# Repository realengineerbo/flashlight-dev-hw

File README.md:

# Flashlight Dev Board Hardware

## Introduction

This repository contains design files for the development board for a flashlight boost driver. The test firmware can be found in the [firmware repository](https://github.com/engineerbo/flashlight-dev-fw).

Also included in the `scripts` subdirectory are Python scripts used to calculate component values during the design process, as well as generate the look-up table for brightness settings.

For a detailed explanation of this project, check out the [video series](https://www.youtube.com/playlist?list=PLYK5tmZIBWtEJjwAFE-49hSeELu9zoAmV) on the [Engineer Bo YouTube channel](https://youtube.com/@engineerbo).

## Features

The development board is designed in [KiCad](https://www.kicad.org/), and features the following:

* ATtiny1616 microcontroller
* MP3432 boost converter
* LED current regulation
  * 1R and 10mR current sense resistances, selectable for high dynamic range (HDR)
  * ATtiny1616 DAC controlled current setpoint
  * Current regulation using TLV333/OPA333 op-amp and MP3432 feedback pin
* Power switch multi-click counting
* Temperature sensing
  * NTC thermistor
  * ATtiny1616 internal temperature sensor
* Battery voltage sensing with low current leakage
* Optional potentiometer for current setpoint (highly experimental)
* Test probe hooks
* Headers for all ATtiny1616 pins
* Many jumpers for testing different configurations

## Usage

This development board is meant to serve as a reference for anybody interested in learning about flashlight boost drivers. It's possible to build these boards, but assembly requires reasonable skill and involves less-than-friendly components e.g. DFN, QFN and many 0402 passives.

Instead, I recommend having a look at the schematics, and leave me a comment on [YouTube](https://www.youtube.com/playlist?list=PLYK5tmZIBWtEJjwAFE-49hSeELu9zoAmV) if you have any questions.

## Hardware Revisions

### Revision A

This is the original design built for testing, and includes a couple of issues:

* GPIO driven P-channel MOSFET for HDR MOSFET gate drive
* MP3432 UVLO not configured
* Wrong footprint for NTC thermistor

These issues and their fixes are explained in detail in the [video series](https://www.youtube.com/playlist?list=PLYK5tmZIBWtEJjwAFE-49hSeELu9zoAmV).

### Revision B

Revision B fixes the issues in Revision A:

* GPIO driven N-channel MOSFET for HDR MOSFET gate drive
* Added MP3432 UVLO

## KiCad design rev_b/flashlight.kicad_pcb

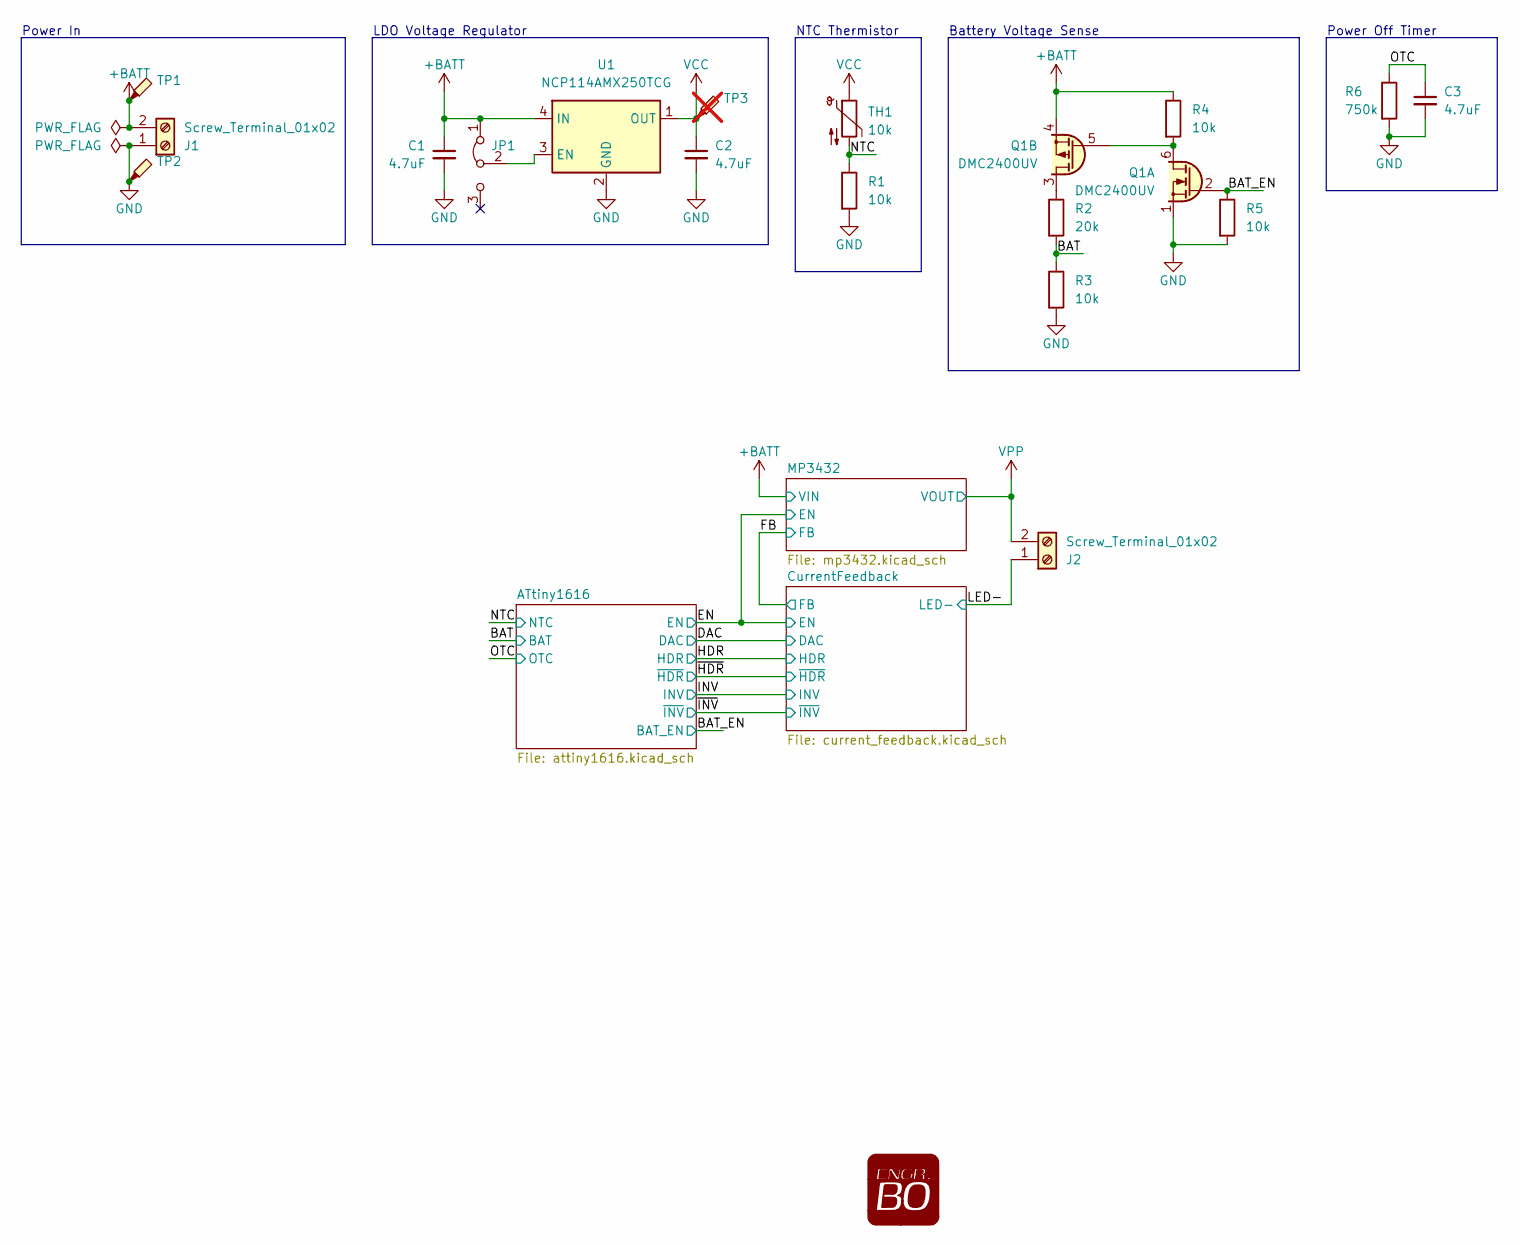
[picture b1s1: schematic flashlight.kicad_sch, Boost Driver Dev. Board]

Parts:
C1, C2, C3: 4.7uF; C_0603_1608Metric; Tolerance X5R; Voltage 16V
J1, J2: Screw_Terminal_01x02; TerminalBlock_Phoenix_MKDS-1,5-2_1x02_P5.00mm_Horizontal
JP1: Jumper_3_Bridged12; PinHeader_1x03_P2.54mm_Vertical
LOGO1: LOGO; logo_6mm
Q1: DMC2400UV; SOT-563
R1, R3, R4, R5: 10k; R_0402_1005Metric; Tolerance 1%
R2: 20k; R_0402_1005Metric; Tolerance 1%
R6: 750k; R_0402_1005Metric; Tolerance 1%
TH1: 10k; R_0402_1005Metric; PartNumber NCP15XH103F03RC
TP1, TP2: TestPoint_Probe; TestPoint_Keystone_5000-5004_Miniature; PartNumber RH-5000
TP3: TestPoint_Probe; TestPoint_Keystone_5000-5004_Miniature; PartNumber RH-5000; not fitted
U1: NCP114AMX250TCG; OnSemi_XDFN4-1EP_1.0x1.0mm_EP0.52x0.52mm; PartNumber NCP114AMX250TCG

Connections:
+BATT: C1.1, J1.2, JP1.1 (A), Q1.4 (S2), R4.1, TP1.1, U1.4 (IN); also elsewhere on the board
/BAT: R2.2, R3.1; also elsewhere on the board
/BAT_EN: Q1.2 (G1), R5.1; also elsewhere on the board
/LED-: J2.1; also elsewhere on the board
/NTC: R1.1, TH1.2; also elsewhere on the board
/OTC: C3.1, R6.1; also elsewhere on the board
GND: C1.2, C2.2, C3.2, J1.1, Q1.1 (S1), R1.2, R3.2, R5.2, R6.2, TP2.1, U1.2 (GND), U1.5 (GND); also elsewhere on the board
unnamed: JP1.2 (C), U1.3 (EN)
unnamed: Q1.5 (G2), Q1.6 (D1), R4.2
unnamed: Q1.3 (D2), R2.1
VCC: C2.1, TH1.1, TP3.1, U1.1 (OUT); also elsewhere on the board
VPP: J2.2; also elsewhere on the board

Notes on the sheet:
NTC Thermistor
Battery Voltage Sense
LDO Voltage Regulator
Power In
Power Off Timer

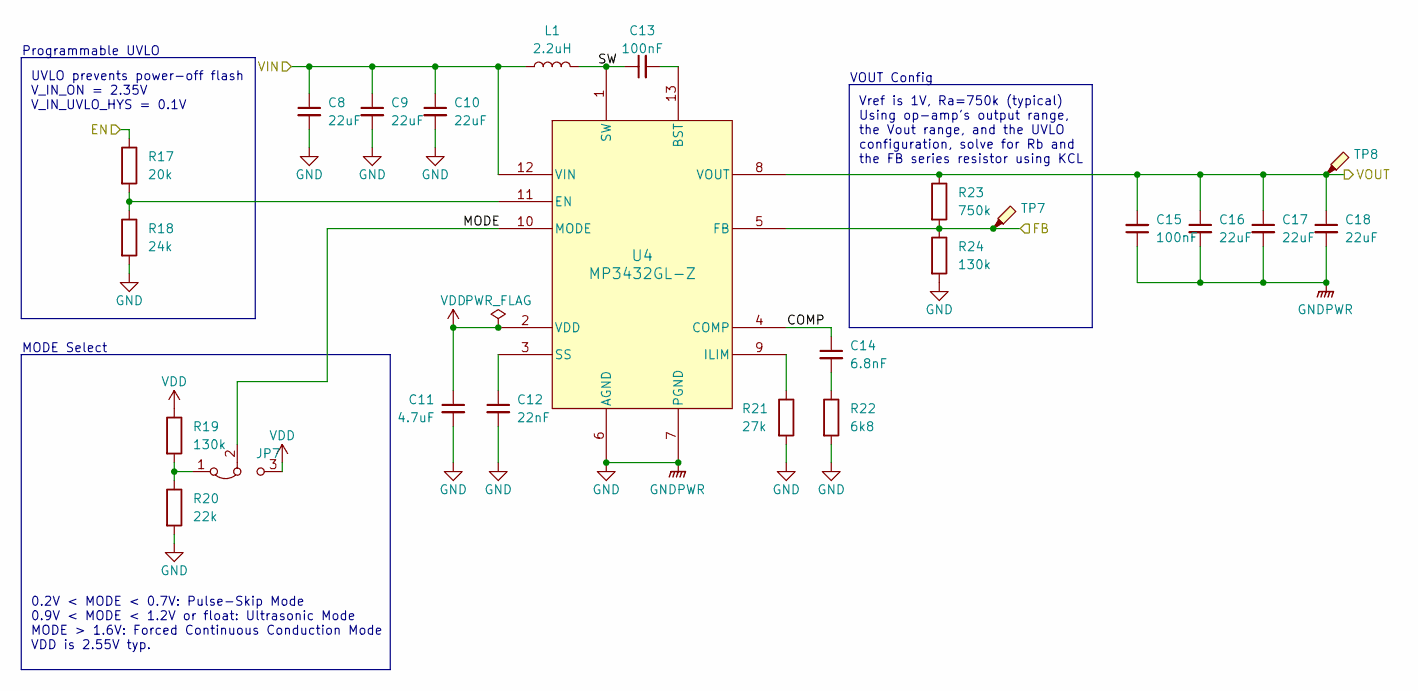
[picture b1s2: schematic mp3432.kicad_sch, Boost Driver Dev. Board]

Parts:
C8, C9, C10, C16, C17, C18: 22uF; C_0805_2012Metric; Tolerance X5R; Voltage 25V
C11: 4.7uF; C_0603_1608Metric; Tolerance X5R; Voltage 16V
C12: 22nF; C_0402_1005Metric
C13, C15: 100nF; C_0402_1005Metric
C14: 6.8nF; C_0402_1005Metric
JP7: Jumper_3_Bridged12; PinHeader_1x03_P2.54mm_Vertical
L1: 2.2uH; L_Coilcraft_XAL7070-XXX; PartNumber XAL7070-222MEC
R17: 20k; R_0402_1005Metric; Tolerance 1%
R18: 24k; R_0402_1005Metric; Tolerance 1%
R19, R24: 130k; R_0402_1005Metric; Tolerance 1%
R20: 22k; R_0402_1005Metric; Tolerance 1%
R21: 27k; R_0402_1005Metric; Tolerance 1%
R22: 6k8; R_0402_1005Metric; Tolerance 1%
R23: 750k; R_0402_1005Metric; Tolerance 1%
TP7, TP8: TestPoint_Probe; TestPoint_Keystone_5000-5004_Miniature; PartNumber RH-5000
U4: MP3432GL-Z; QFN-13_MP3431_MNP; PartNumber MP3432GL-Z

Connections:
+BATT: C8.1, C9.1, C10.1, L1.1, U4.12 (VIN); also elsewhere on the board
/EN: R17.1; also elsewhere on the board
/FB: R23.2, R24.1, TP7.1, U4.5 (FB); also elsewhere on the board
/MP3432/COMP: C14.1, U4.4 (COMP)
/MP3432/MODE: JP7.2 (C), U4.10 (MODE)
/MP3432/SW: C13.1, L1.2, U4.1 (SW)
GND: C8.2, C9.2, C10.2, C11.2, C12.2, C15.1, C16.2, C17.2, C18.2, R18.2, R20.2, R21.2, R22.2, R24.2, U4.6 (AGND), U4.7 (PGND); also elsewhere on the board
unnamed: C14.2, R22.1
unnamed: JP7.1 (A), R19.2, R20.1
unnamed: C13.2, U4.13 (BST)
unnamed: R17.2, R18.1, U4.11 (EN)
unnamed: R21.1, U4.9 (ILIM)
unnamed: C12.1, U4.3 (SS)
VDD: C11.1, JP7.3 (B), R19.1, U4.2 (VDD)
VPP: C15.2, C16.1, C17.1, C18.1, R23.1, TP8.1, U4.8 (VOUT); also elsewhere on the board

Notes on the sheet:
Vref is 1V, Ra=750k (typical) Using op-amp's output range, the Vout range, and the UVLO configuration, solve for Rb and the FB series resistor using KCL
0.2V < MODE < 0.7V: Pulse-Skip Mode 0.9V < MODE < 1.2V or float: Ultrasonic Mode MODE > 1.6V: Forced Continuous Conduction Mode VDD is 2.55V typ.
MODE Select
UVLO prevents power-off flash V_IN_ON = 2.35V V_IN_UVLO_HYS = 0.1V
Programmable UVLO
VOUT Config

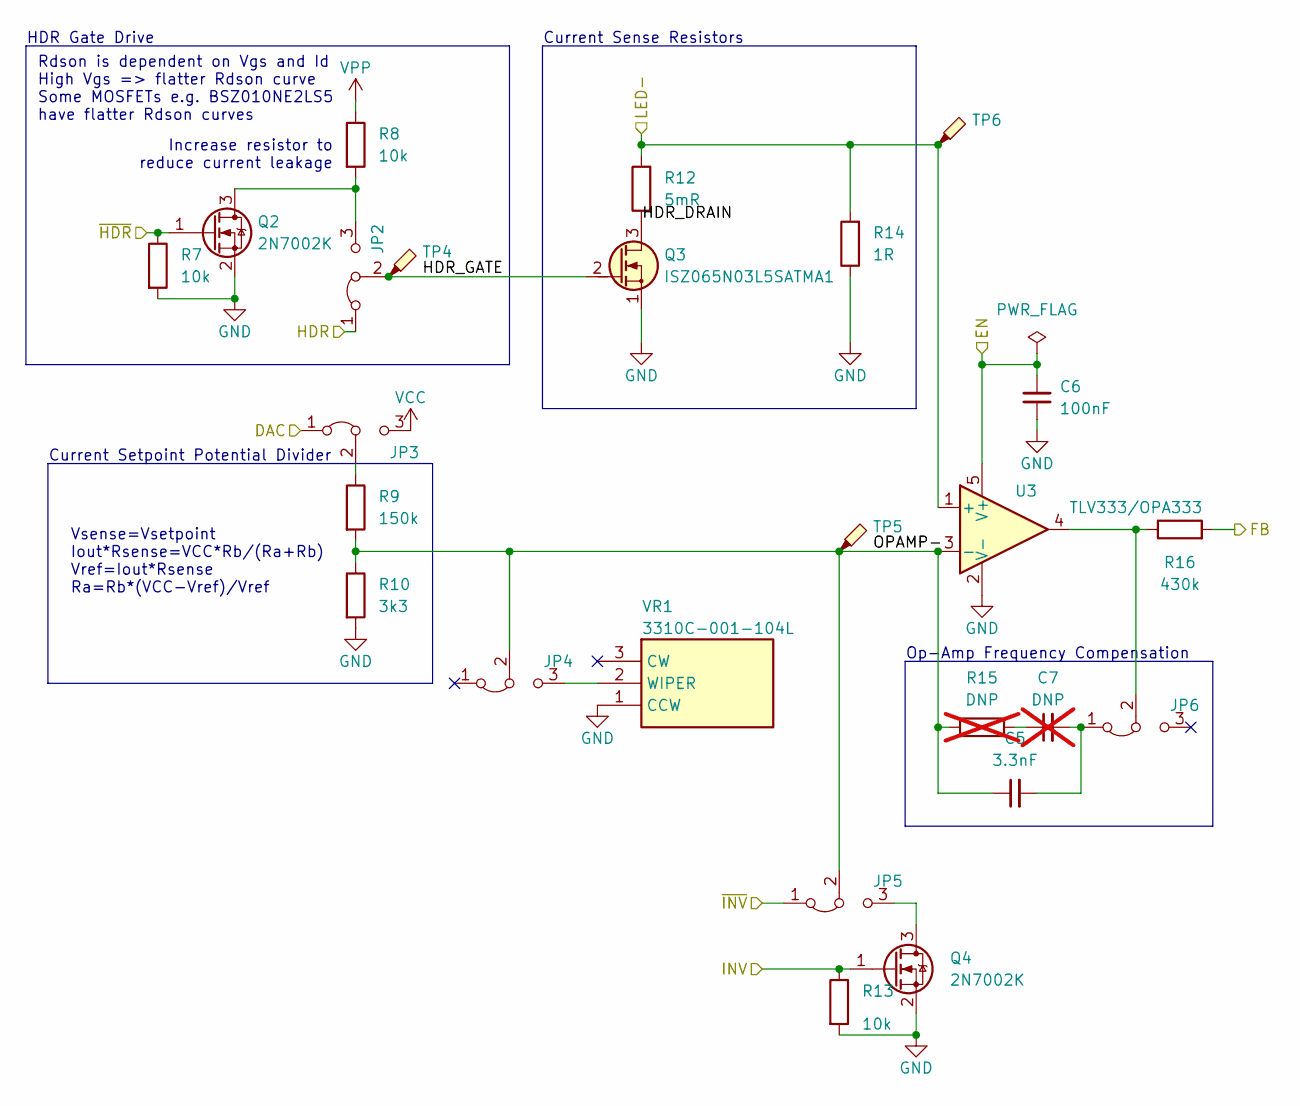
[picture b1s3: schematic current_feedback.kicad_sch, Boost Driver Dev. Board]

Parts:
C5: 3.3nF; C_0402_1005Metric; Tolerance C0G
C6: 100nF; C_0402_1005Metric
C7: DNP; C_0402_1005Metric; Tolerance C0G; not fitted
JP2, JP3, JP4, JP5, JP6: Jumper_3_Bridged12; PinHeader_1x03_P2.54mm_Vertical
Q2, Q4: 2N7002K; SOT-23
Q3: ISZ065N03L5SATMA1; Infineon_PG_TSDSON-8_FL; PartNumber ISZ065N03L5SATMA1
R7, R8, R13: 10k; R_0402_1005Metric; Tolerance 1%
R9: 150k; R_0402_1005Metric; Tolerance 1%
R10: 3k3; R_0402_1005Metric; Tolerance 1%
R12: 5mR; R_0805_2012Metric; Tolerance 1%
R14: 1R; R_0805_2012Metric; Tolerance 1%
R15: DNP; R_0402_1005Metric; Tolerance 1%; not fitted
R16: 430k; R_0402_1005Metric; Tolerance 1%
TP4, TP5, TP6: TestPoint_Probe; TestPoint_Keystone_5000-5004_Miniature; PartNumber RH-5000
U3: TLV333/OPA333; SOT-353_SC-70-5; PartNumber TLV333IDCKR
VR1: 3310C-001-104L; 3310C001503L; Mouser Part Number 652-3310C-001-104L

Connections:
/CurrentFeedback/HDR_DRAIN: Q3.3 (D), R12.1
/CurrentFeedback/HDR_GATE: JP2.2 (C), Q3.2 (G), TP4.1
/CurrentFeedback/OPAMP-: C5.1, JP4.2 (C), JP5.2 (C), R9.2, R10.1, R15.1, TP5.1, U3.3 (-)
/DAC: JP3.1 (A); also elsewhere on the board
/EN: C6.2, U3.5 (V+); also elsewhere on the board
/FB: R16.2; also elsewhere on the board
/HDR: JP2.1 (A); also elsewhere on the board
/INV: Q4.1 (G), R13.1; also elsewhere on the board
/LED-: R12.2, R14.2, TP6.1, U3.1 (+); also elsewhere on the board
/~HDR: Q2.1 (G), R7.1; also elsewhere on the board
/~INV: JP5.1 (A); also elsewhere on the board
GND: C6.1, Q2.2 (S), Q3.1 (S), Q4.2 (S), R7.2, R10.2, R13.2, R14.1, U3.2 (V-), VR1.1 (CCW); also elsewhere on the board
unnamed: C7.1, R15.2
unnamed: JP2.3 (B), Q2.3 (D), R8.2
unnamed: JP3.2 (C), R9.1
unnamed: JP4.3 (B), VR1.2 (WIPER)
unnamed: JP5.3 (B), Q4.3 (D)
unnamed: C5.2, C7.2, JP6.1 (A)
unnamed: JP6.2 (C), R16.1, U3.4
VCC: JP3.3 (B); also elsewhere on the board
VPP: R8.1; also elsewhere on the board

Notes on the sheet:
Current Setpoint Potential Divider
HDR Gate Drive
Vsense=Vsetpoint Iout*Rsense=VCC*Rb/(Ra+Rb) Vref=Iout*Rsense Ra=Rb*(VCC-Vref)/Vref
Increase resistor to reduce current leakage
Rdson is dependent on Vgs and Id High Vgs => flatter Rdson curve Some MOSFETs e.g. BSZ010NE2LS5 have flatter Rdson curves
Op-Amp Frequency Compensation
Current Sense Resistors

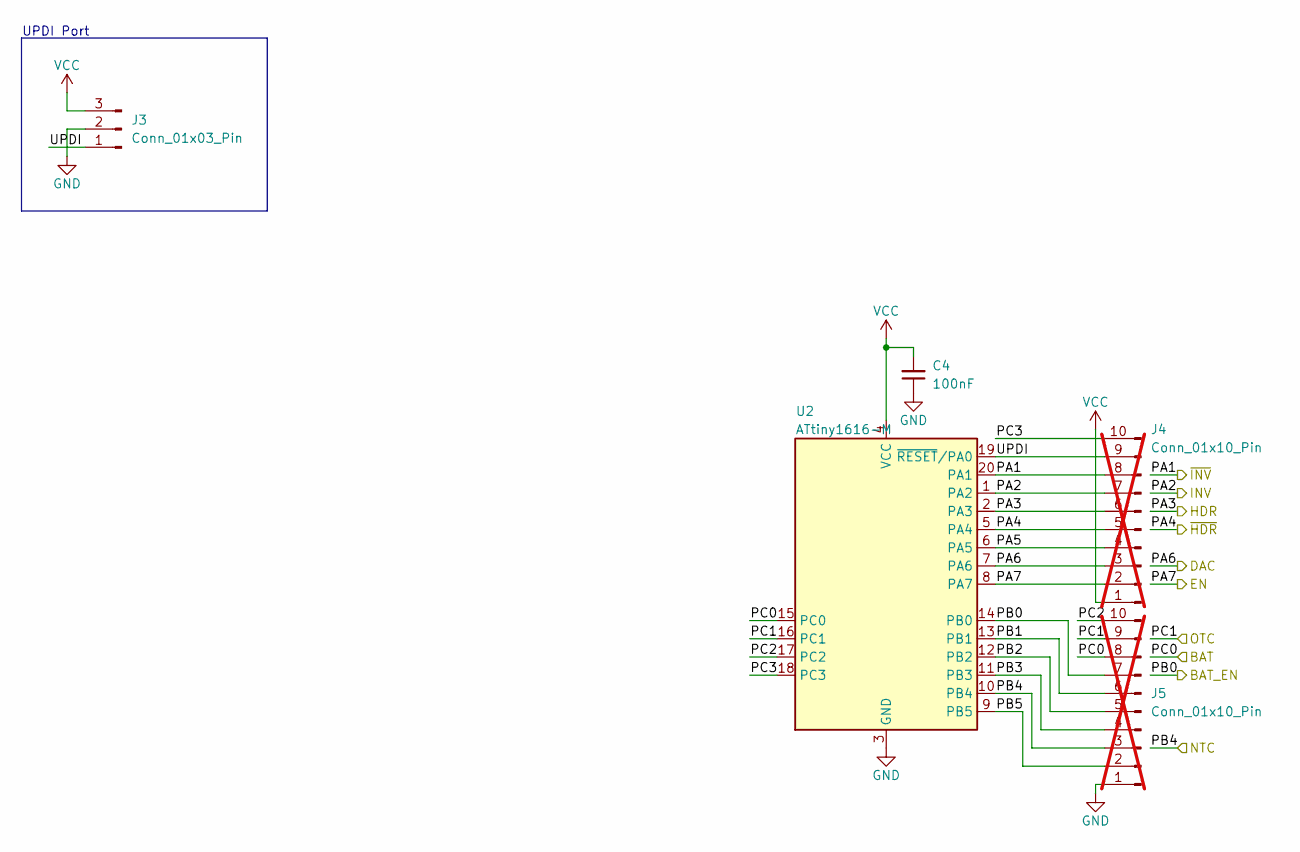
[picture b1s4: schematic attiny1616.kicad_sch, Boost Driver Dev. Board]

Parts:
C4: 100nF; C_0402_1005Metric
J3: Conn_01x03_Pin; PinHeader_1x03_P2.54mm_Vertical
J4, J5: Conn_01x10_Pin; PinHeader_1x10_P2.54mm_Vertical; not fitted
U2: ATtiny1616-M; VQFN-20-1EP_3x3mm_P0.4mm_EP1.7x1.7mm; PartNumber ATTINY1616-MNR

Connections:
/ATtiny1616/PA5: J4.4, U2.6 (PA5)
/ATtiny1616/PB1: J5.6, U2.13 (PB1)
/ATtiny1616/PB2: J5.5, U2.12 (PB2)
/ATtiny1616/PB3: J5.4, U2.11 (PB3)
/ATtiny1616/PB5: J5.2, U2.9 (PB5)
/ATtiny1616/PC2: J5.10, U2.17 (PC2)
/ATtiny1616/PC3: J4.10, U2.18 (PC3)
/ATtiny1616/UPDI: J3.1, J4.9, U2.19 (~RESET/PA0)
/BAT: J5.8, U2.15 (PC0); also elsewhere on the board
/BAT_EN: J5.7, U2.14 (PB0); also elsewhere on the board
/DAC: J4.3, U2.7 (PA6); also elsewhere on the board
/EN: J4.2, U2.8 (PA7); also elsewhere on the board
/HDR: J4.6, U2.2 (PA3); also elsewhere on the board
/INV: J4.7, U2.1 (PA2); also elsewhere on the board
/NTC: J5.3, U2.10 (PB4); also elsewhere on the board
/OTC: J5.9, U2.16 (PC1); also elsewhere on the board
/~HDR: J4.5, U2.5 (PA4); also elsewhere on the board
/~INV: J4.8, U2.20 (PA1); also elsewhere on the board
GND: C4.1, J3.2, J5.1, U2.3 (GND), U2.21 (GND); also elsewhere on the board
VCC: C4.2, J3.3, J4.1, U2.4 (VCC); also elsewhere on the board

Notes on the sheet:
UPDI Port

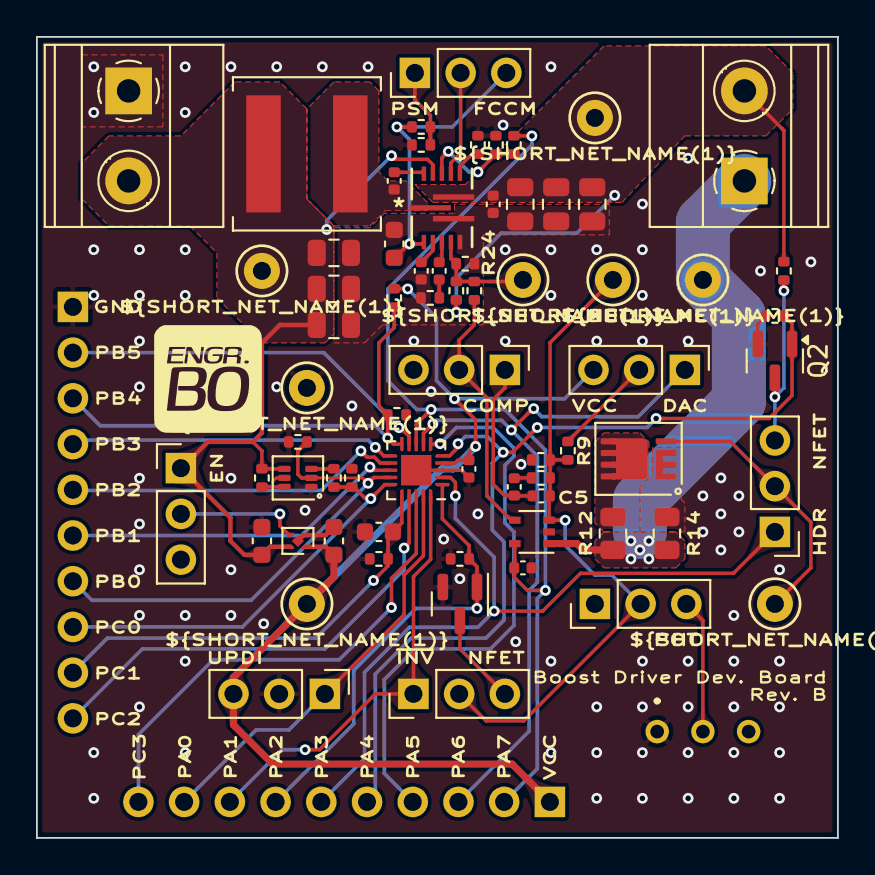
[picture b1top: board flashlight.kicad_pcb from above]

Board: 4 copper layers, 44.5 x 44.5 mm, 73 parts (0 on the bottom side), 47 nets.

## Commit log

2024-03-29 Squash for release.
2025-03-26 Fix minor typo.
